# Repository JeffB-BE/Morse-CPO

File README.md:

# Morse-CPO
Twin-T Oscillator design based upon the work by Michael A. Maynard (K4ICY).

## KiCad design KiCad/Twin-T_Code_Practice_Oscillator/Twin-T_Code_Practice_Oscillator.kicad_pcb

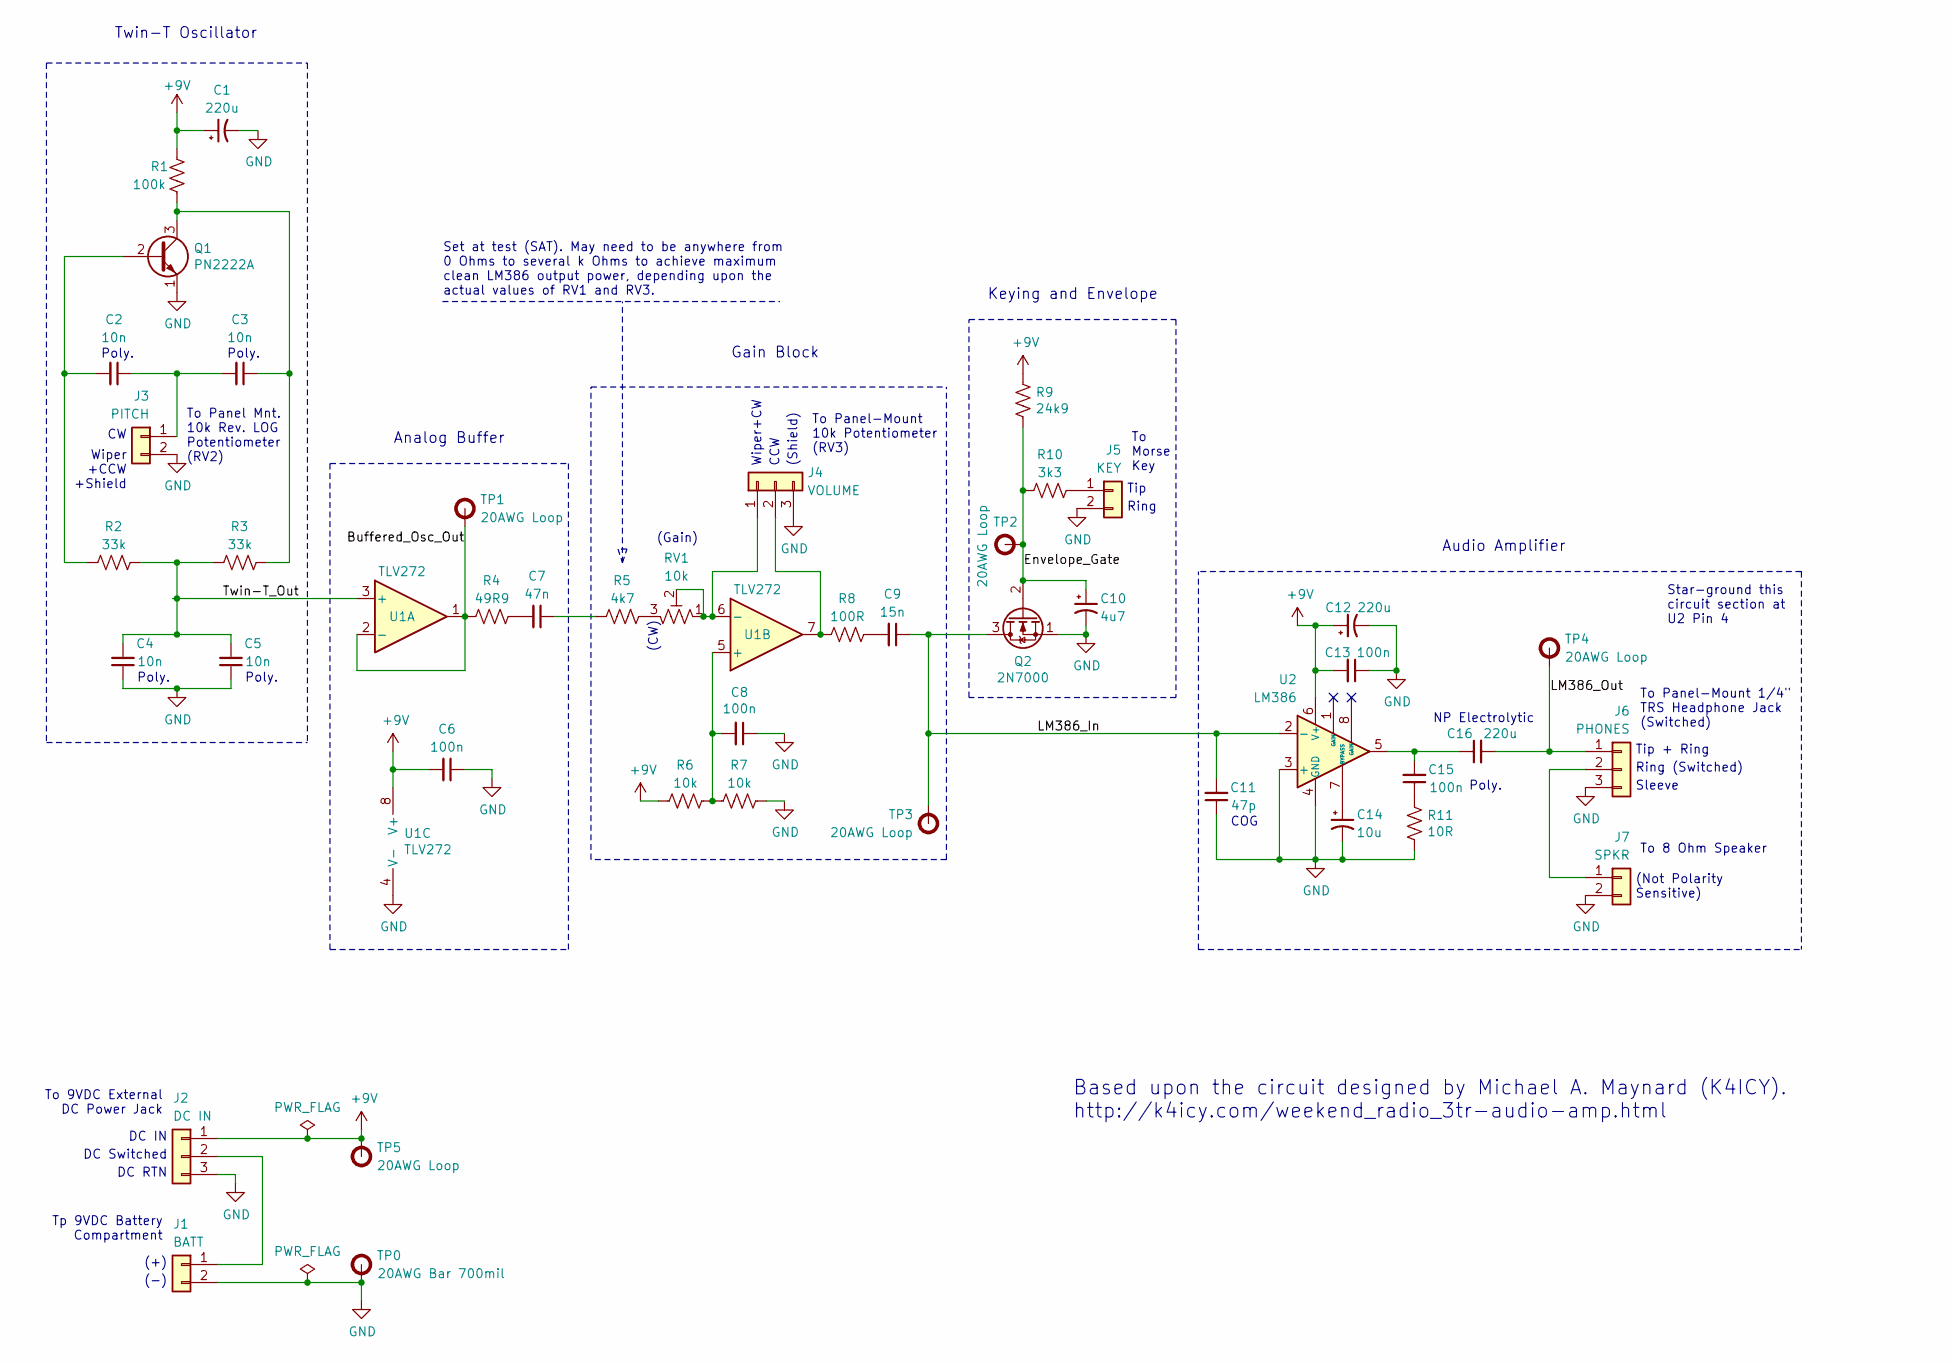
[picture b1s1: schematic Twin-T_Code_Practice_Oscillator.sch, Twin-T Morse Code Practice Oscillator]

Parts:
C1, C12: 220u; BE_Cap_Round_D6.3mm_H11.2mm_P2.5mm
C2, C3, C4, C5: 10n; BE_Cap_Rect-Film_W7.2mm_T2.5mm_H6.5mm_P5.0mm
C6, C8, C13: 100n; BE_Cap_MLCC_95milx150mil_P100mil
C7: 47n; BE_Cap_Rect-Film_W7.2mm_T2.5mm_H6.5mm_P5.0mm
C9: 15n; BE_Cap_Rect-Film_W7.2mm_T2.5mm_H6.5mm_P5.0mm
C10: 4u7; BE_Cap_Round_D3.0mm_P2.54mm
C11: 47p; BE_Cap_Dipped_W4.0mm_T2.6mm_H5.6mm_P2.5mm
C14: 10u; BE_Cap_Round_D4.0mm_H5.0mm_P2.54mm
C15: 100n; BE_Cap_Rect-Film_W7.2mm_T2.5mm_H6.5mm_P5.0mm
C16: 220u; BE_Cap_Round-NP_D10.0mm_H12.5mm_P5.0mm
J1: BATT; BE_Conn_HDR_SIP-2
J2: DC IN; BE_Conn_HDR_SIP-3
J3: PITCH; BE_Conn_HDR_SIP-2
J4: VOLUME; BE_Conn_HDR_SIP-3
J5: KEY; BE_Conn_HDR_SIP-2
J6: PHONES; BE_Conn_HDR_SIP-3
J7: SPKR; BE_Conn_HDR_SIP-2
Q1: PN2222A; TO92-3_Formed_Leads
Q2: 2N7000; TO92-3_Formed_Leads
R1: 100k; BE_Resistor_THT_Axial_.100x.400
R2, R3: 33k; BE_Resistor_THT_Axial_.100x.400
R4: 49R9; BE_Resistor_THT_Axial_.100x.400
R5: 4k7; BE_Resistor_THT_Axial_.100x.400
R6, R7: 10k; BE_Resistor_THT_Axial_.100x.400
R8: 100R; BE_Resistor_THT_Axial_.100x.400
R9: 24k9; BE_Resistor_THT_Axial_.100x.400
R10: 3k3; BE_Resistor_THT_Axial_.100x.400
R11: 10R; BE_Resistor_THT_Axial_.100x.400
RV1: 10k; Piher_PT6_Vertical
TP0: 20AWG Bar 700mil; BE_TP-Bar_20AWG_L700mil
TP1, TP2, TP3, TP4, TP5: 20AWG Loop; BE_TP-Loop_20AWG_D200MIL
U1: TLV272; BE_DIP-8_Socket
U2: LM386; BE_DIP-8_Socket

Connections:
+9V: C1.1, C6.2, C12.1, C13.2, J2.1, R1.2, R6.1, R9.1, TP5.1, U1.8 (V+), U2.6 (V+)
/Buffered_Osc_Out: R4.1, TP1.1, U1.1, U1.2 (-)
/Envelope_Gate: C10.1, Q2.2 (G), R9.2, R10.1, TP2.1
/LM386_In: C9.1, C11.2, Q2.3 (D), TP3.1, U2.2 (-)
/LM386_Out: C16.2, J6.1, TP4.1
/Twin-T_Out: C4.2, C5.2, R2.2, R3.1, U1.3 (+)
GND: C1.2, C4.1, C5.1, C6.1, C8.1, C10.2, C11.1, C12.2, C13.1, C14.2, J1.2, J2.3, J3.2, J4.3, J5.2, J6.3, J7.2, Q1.1 (E), Q2.1 (S), R7.2, R11.2, TP0.1, U1.4 (V-), U2.3 (+), U2.4 (GND)
unnamed: C2.1, C3.2, J3.1
unnamed: C2.2, Q1.2 (B), R2.1
unnamed: C3.1, Q1.3 (C), R1.1, R3.2
unnamed: C7.1, R5.1
unnamed: C7.2, R4.2
unnamed: C8.2, R6.2, R7.1, U1.5 (+)
unnamed: C9.2, R8.2
unnamed: C14.1, U2.7 (BYPASS)
unnamed: C15.1, R11.1
unnamed: C15.2, C16.1, U2.5
unnamed: J1.1, J2.2
unnamed: J4.1, RV1.1, RV1.2, U1.6 (-)
unnamed: J4.2, R8.1, U1.7
unnamed: J5.1, R10.2
unnamed: J6.2, J7.1
unnamed: R5.2, RV1.3

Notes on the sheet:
To Panel-Mount 1/4" TRS Headphone Jack (Switched)
Sleeve
Ring (Switched)
Tip + Ring
DC IN
DC Switched
DC RTN
To 9VDC External DC Power Jack
Tp 9VDC Battery Compartment
(+)
(-)
To 8 Ohm Speaker
Wiper +CCW +Shield
To Panel Mnt. 10k Rev. LOG Potentiometer (RV2)
To Panel-Mount 10k Potentiometer (RV3)
To Morse Key
NP Electrolytic
COG
Poly.
(Not Polarity Sensitive)
Based upon the circuit designed by Michael A. Maynard (K4ICY). http://k4icy.com/weekend_radio_3tr-audio-amp.html
Wiper+CW
CCW
(Gain)
(CW)
Twin-T Oscillator
Analog Buffer
Gain Block
Audio Amplifier
Tip
Ring
(Shield)
Star-ground this circuit section at U2 Pin 4
Keying and Envelope
Set at test (SAT). May need to be anywhere from 0 Ohms to several k Ohms to achieve maximum clean LM386 output power, depending upon the actual values of RV1 and RV3.

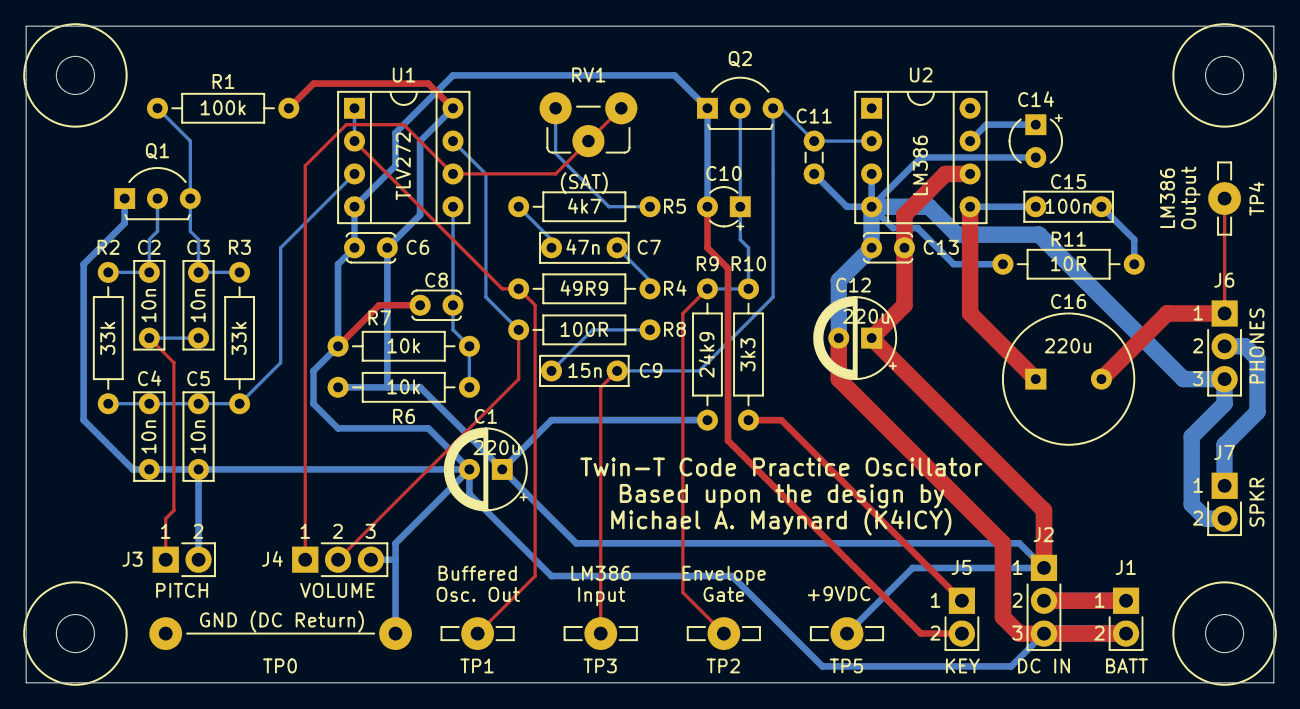
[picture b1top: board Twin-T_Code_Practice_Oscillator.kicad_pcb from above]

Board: 2 copper layers, 96.5 x 50.8 mm, 49 parts (0 on the bottom side), 23 nets.

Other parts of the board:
MH1, MH2, MH3, MH4: BE_Nbr-4_Thru_Hole; BE_Nbr-4_Mounting_Hole

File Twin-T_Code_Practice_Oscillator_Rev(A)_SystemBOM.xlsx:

Item | Qty | References | Value | Lead Spacing | Type | Mfrg. | Manufacturer P/N | Distributor | Dist. P/N | Status | Datasheet
1 | 1 | C11 | 47p | 100mil (2.5mm) | MLCC, C0G | Vishay-Sprague | 1C10C0G470J050B | Mouser | 75-1C10C0G470J050B |  | https://www.mouser.com/datasheet/2/427/Sprague%201C-3C%20MLC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
2 | 3 | C6, C8, C13 | 100n | 100mil (2.5mm) | MLCC, X7R | Vishay | K103K15X7RF53L2 | Mouser | 594-K103K15X7RF53L2 |  | https://www.vishay.com/docs/45171/kseries.pdf
3 | 4 | C2, C3, C4, C5 | 10n | 200 mil (5mm) | Polyester Film | Kemet | MMK5103J63J01L16.5 | Mouser | 80-MMK5103J63J01TR18 |  | https://content.kemet.com/datasheets/F3294_MMK.pdf
4 | 1 | C7 | 47n | 200 mil (5mm) | Polyester Film | Kemet | MMK5473J63J01L4 | Mouser | 80-MMK5473J63J01L4 |  | https://content.kemet.com/datasheets/F3294_MMK.pdf
5 | 1 | C9 | 15n | 200 mil (5mm) | Polyester Film | Kemet | MMK5153J63J01L16.5 | Mouser | 80-MMK5153J63J01TR16 |  | https://content.kemet.com/datasheets/F3294_MMK.pdf
6 | 1 | C15 | 100n | 200 mil (5mm) | Polyester Film | Kemet | MMK5104J63J01L4 | Mouser | 80-MMK5104J63J01L4 |  | https://content.kemet.com/datasheets/F3294_MMK.pdf
7 | 1 | C16 | 220u | 200 mil (5mm) | Non-Polarized Electrolytic | Panasonic | ECE-A1CN221XB | Mouser | 667-ECE-A1CN221XB |  | https://industrial.panasonic.com/cdbs/www-data/pdf/RDF0000/A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
8 | 1 | C10 | 4u7 | 100mil (2.5mm) | Electrolytic | Nichicon | UMA1C4R7MCD2TP | Mouser | 647-UMA1C4R7MCD2TP |  | https://www.nichicon.co.jp/english/products/pdfs/e-uma.pdf
9 | 1 | C14 | 10u | 100mil (2.5mm) | Electrolytic | Nichicon | UMA1C100MDD | Mouser | 647-UMA1C100MDD |  | https://www.nichicon.co.jp/english/products/pdfs/e-uma.pdf
10 | 2 | C1, C12 | 220u | 100mil (2.5mm) | Electrolytic | Panasonic | EEU-FR1C221 | Mouser | 667-EEU-FR1C221 |  | https://industrial.panasonic.com/cdbs/www-data/pdf/RDF0000/A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
11 | 2 | R2, R3 | 33k | (Axial) | Metal Film, 1/4W 1% | Yageo | MFR-25FBF52-33K | Mouser | 603-MFR-25FBF52-33K |  | https://www.yageo.com/upload/media/product/products/datashee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
12 | 2 | R6, R7 | 10k | (Axial) | Metal Film, 1/4W 1% | Yageo | MFR-25FBF52-10K | Mouser | 603-MFR-25FBF52-10K |  | https://www.yageo.com/upload/media/product/products/datashee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
13 | 1 | R1 | 100k | (Axial) | Metal Film, 1/4W 1% | Yageo | MFR-25FBF52-100K | Mouser | 603-MFR-25FBF52-100K |  | https://www.yageo.com/upload/media/product/products/datashee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
14 | 1 | R4 | 49R9 | (Axial) | Metal Film, 1/4W 1% | Yageo | MFR-25FBF52-49R9 | Mouser | 603-MFR-25FBF52-49R9 |  | https://www.yageo.com/upload/media/product/products/datashee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
15 | 1 | R5 | 4k7 | (Axial) | Metal Film, 1/4W 1% | Yageo | MFR-25FBF52-4k7 | Mouser | 603-MFR-25FBF52-4K7 |  | https://www.yageo.com/upload/media/product/products/datashee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
16 | 1 | R8 | 100R | (Axial) | Metal Film, 1/4W 1% | Yageo | MFR-25FBF52-100R | Mouser | 603-MFR-25FBF52-100R |  | https://www.yageo.com/upload/media/product/products/datashee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
17 | 1 | R9 | 24k9 | (Axial) | Metal Film, 1/4W 1% | Yageo | MFR-25FBF52-24k9 | Mouser | 603-MFR-25FBF52-24K9 |  | https://www.yageo.com/upload/media/product/products/datashee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
18 | 1 | R10 | 3k3 | (Axial) | Metal Film, 1/4W 1% | Yageo | MFR-25FBF52-3K3 | Mouser | 603-MFR-25FBF52-3K3 |  | https://www.yageo.com/upload/media/product/products/datashee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
19 | 1 | R11 | 10R | (Axial) | Metal Film, 1/4W 1% | Yageo | MFR-25FBF52-10R | Mouser | 603-MFR-25FBF52-10R |  | https://www.yageo.com/upload/media/product/products/datashee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
20 | 1 | U1 | TLV272 | DIP-8 | Dual Op-Amp | TI | TLV272IP | Mouser | 595-TLV272IP |  | https://www.ti.com/lit/ds/symlink/tlv272.pdf
21 | 1 | U2 | LM386 | DIP-8 | Audio Amplifier | TI | LM386MX-1/NOPB | Mouser | 926-LM386MX-1/NOPB |  | https://www.ti.com/lit/ds/symlink/lm386.pdf
22 | 1 | TP0 | 20AWG Bar 700mil | 700mil (18mm) | Hand-made from 20AWG (0.8mm) solid wire | (custom) | - | - | - |  | -
23 | 5 | TP1, TP2, TP3, TP4, TP5 | 20AWG Loop | (single lead) | Hand-made from 20AWG (0.8mm) solid wire | (custom) | - | - | - |  | -
24 | 1 | RV1 | 10k | 100x100mil (2.5mm) | Single-turn vertical trimpot | Amphenol Piher | PT6KH-103A2020 | Mouser | 531-PT6KH-10K |  | https://www.mouser.com/datasheet/2/18/11-PT6v03-1499160.pdf
25 | 1 | Q1 | PN2222A | TO-92 100mil (2.5mm) | BJT, NPN | Fairchild | PN2222ATA | Mouser | 512-PN2222ATA |  | http://www.fairchildsemi.com/ds/PN/PN2222A.pdf
26 | 1 | Q2 | 2N7000 | TO-92 100mil (2.5mm) | MOSFET, N-Channel | Fairchild | 2N7000 | Mouser | 512-2N7000 |  | https://www.fairchildsemi.com/datasheets/2N/2N7000.pdf
27 | 1 | J1, J3, J5, J7 |  | 100mil (2.5mm) | Header, unshrouded, SIP, 2-position | Molex | 22-28-4020 | Mouser | 538-22-28-4020 |  | https://www.molex.com/pdm_docs/sd/022284364_sd.pdf
28 | 1 | J2, J4, J6 |  | 100mil (2.5mm) | Header, unshrouded, SIP, 3-position | Molex | 22-28-4030 | Mouser | 538-22-28-4030 |  | https://www.molex.com/pdm_docs/sd/022284364_sd.pdf

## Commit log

2020-08-30 Initial commit of Rev(A)
2020-09-02 Swapped LM386 inputs, tweaked PCB layout, updated BOM
2020-09-02 Replaced RV1. Cleaned up all docs
2020-09-03 Fixed small error in volume pot placement
